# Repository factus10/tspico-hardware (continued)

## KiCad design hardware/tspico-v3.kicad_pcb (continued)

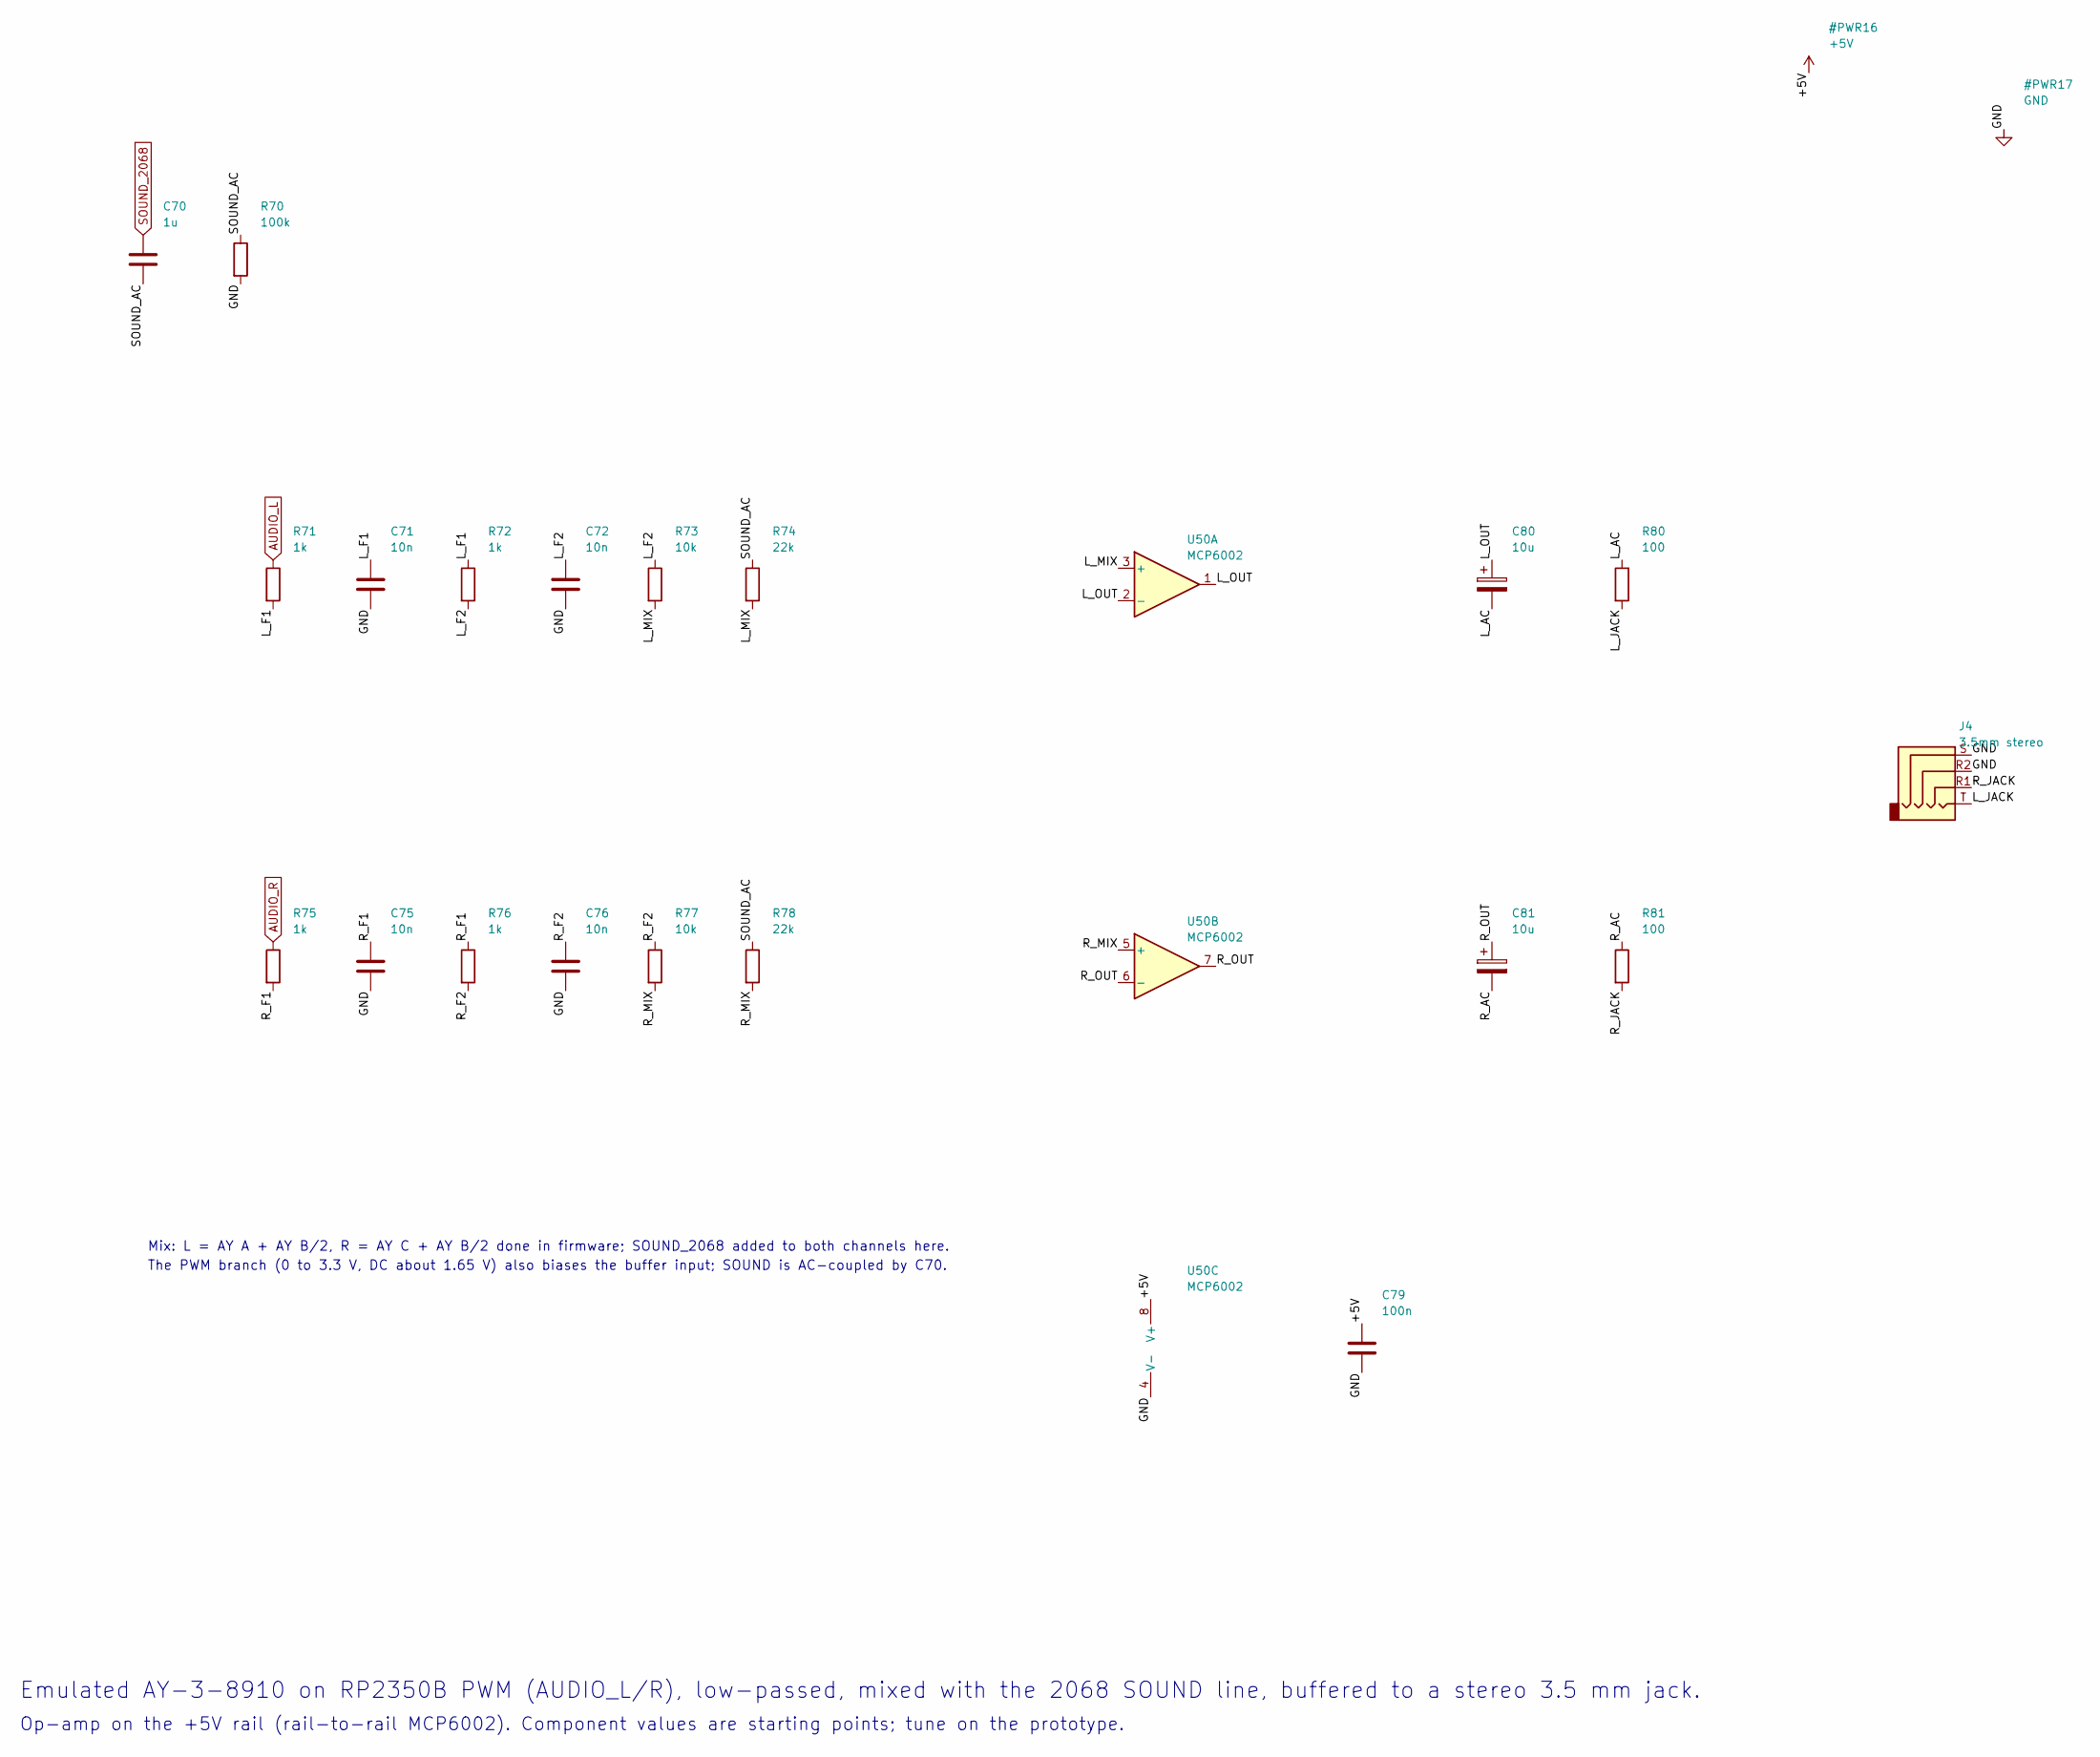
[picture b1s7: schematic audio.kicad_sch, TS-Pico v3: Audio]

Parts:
C70: 1u; C_0603_1608Metric; MPN CL10A105KB8NNNC; LCSC C15849
C71, C72, C75, C76: 10n; C_0603_1608Metric; MPN CL10B103KB8NNNC; LCSC C57112
C79: 100n; C_0603_1608Metric; MPN CC0603KRX7R9BB104; LCSC C14663
C80, C81: 10u; C_0603_1608Metric; MPN CL10A106KP8NNNC; LCSC C19702
J4: 3.5mm stereo; Jack_3.5mm_PJ320D_Horizontal; MPN PJ-320D; LCSC C431535
R70: 100k; R_0603_1608Metric; MPN 0603WAF1003T5E; LCSC C25803
R71, R72, R75, R76: 1k; R_0603_1608Metric; MPN 0603WAF1001T5E; LCSC C21190
R73, R77: 10k; R_0603_1608Metric; MPN 0603WAF1002T5E; LCSC C25804
R74, R78: 22k; R_0603_1608Metric; MPN 0603WAF2202T5E; LCSC C31850
R80, R81: 100; R_0603_1608Metric; MPN 0603WAF1000T5E; LCSC C22775
U50: MCP6002; SOIC-8_3.9x4.9mm_P1.27mm; MPN MCP6002T-I/SN; LCSC C7377

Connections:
+5V: C79.1, U50.8 (V+); also elsewhere on the board
/Audio/L_AC: C80.2, R80.1
/Audio/L_F1: C71.1, R71.2, R72.1
/Audio/L_F2: C72.1, R72.2, R73.1
/Audio/L_JACK: J4.T, R80.2
/Audio/L_MIX: R73.2, R74.2, U50.3 (+)
/Audio/L_OUT: C80.1, U50.1, U50.2 (-)
/Audio/R_AC: C81.2, R81.1
/Audio/R_F1: C75.1, R75.2, R76.1
/Audio/R_F2: C76.1, R76.2, R77.1
/Audio/R_JACK: J4.R1, R81.2
/Audio/R_MIX: R77.2, R78.2, U50.5 (+)
/Audio/R_OUT: C81.1, U50.6 (-), U50.7
/Audio/SOUND_AC: C70.2, R70.1, R74.1, R78.1
AUDIO_L: R71.1; also elsewhere on the board
AUDIO_R: R75.1; also elsewhere on the board
SOUND_2068: C70.1; also elsewhere on the board

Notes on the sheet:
Emulated AY-3-8910 on RP2350B PWM (AUDIO_L/R), low-passed, mixed with the 2068 SOUND line, buffered to a stereo 3.5 mm jack.
Op-amp on the +5V rail (rail-to-rail MCP6002). Component values are starting points; tune on the prototype.
Mix: L = AY A + AY B/2, R = AY C + AY B/2 done in firmware; SOUND_2068 added to both channels here.
The PWM branch (0 to 3.3 V, DC about 1.65 V) also biases the buffer input; SOUND is AC-coupled by C70.

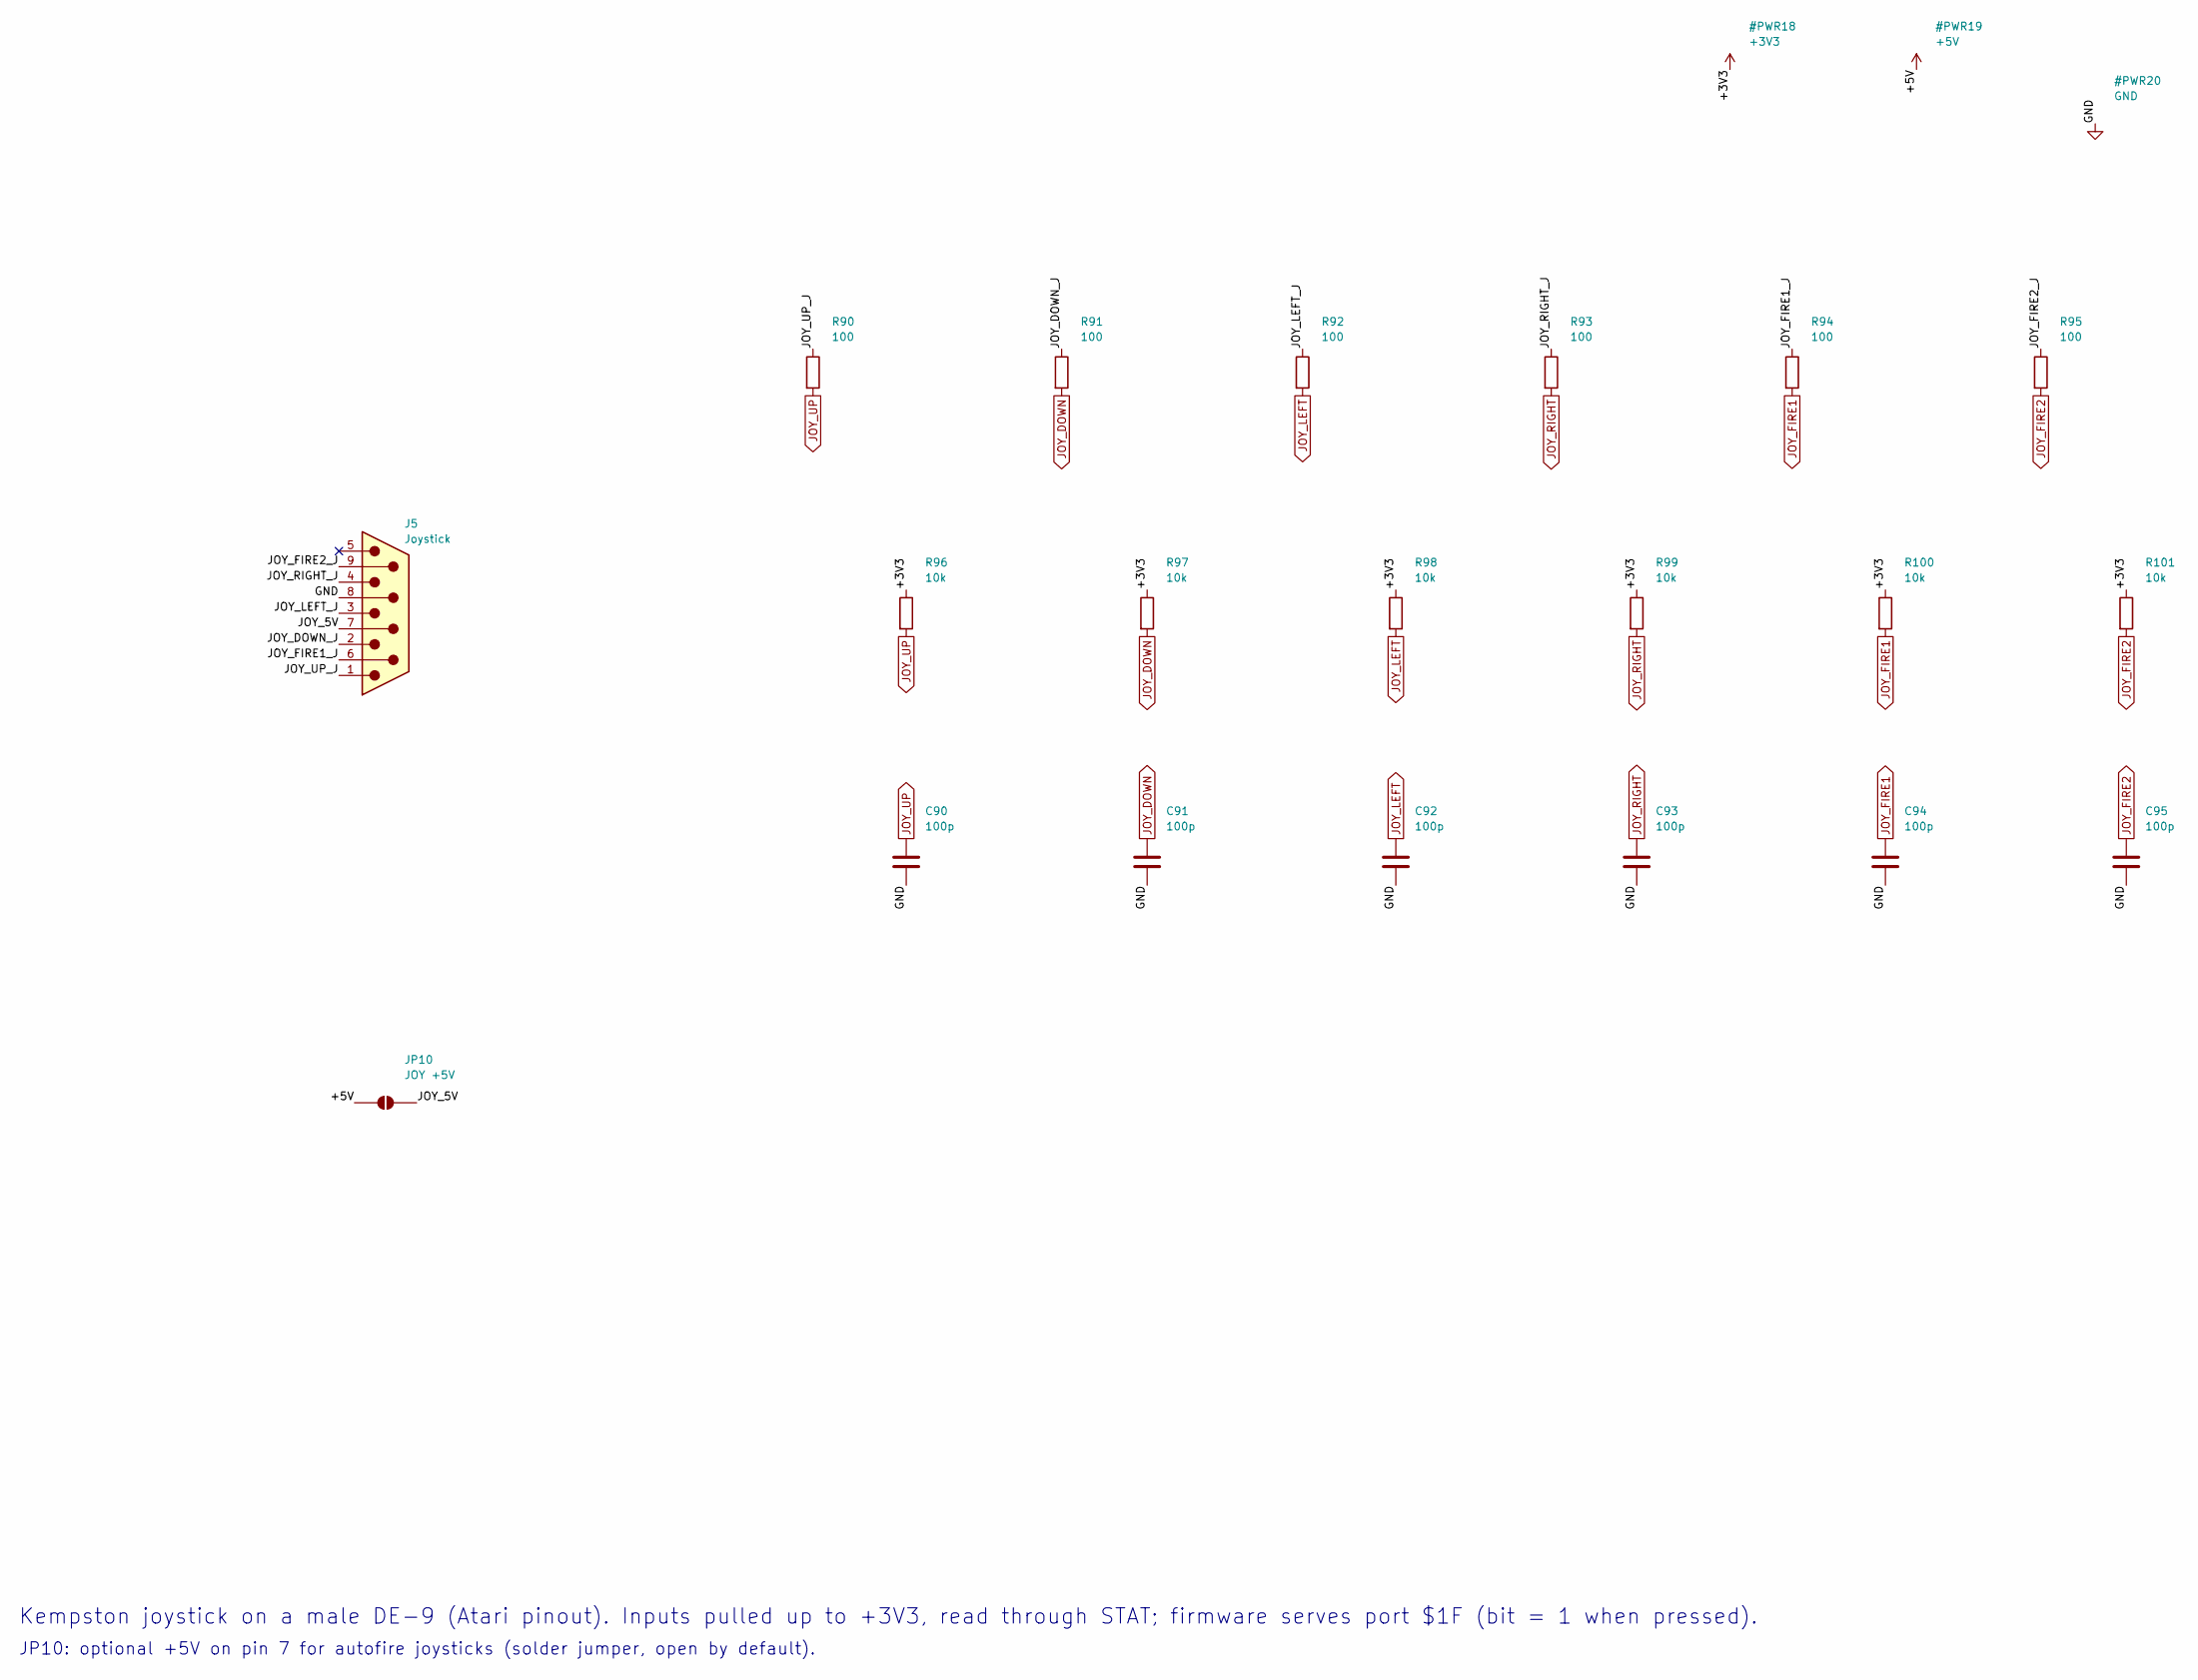
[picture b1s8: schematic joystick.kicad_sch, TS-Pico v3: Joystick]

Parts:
C90, C91, C92, C93, C94, C95: 100p; C_0603_1608Metric; MPN CL10C101JB8NNNC; LCSC C14858
J5: Joystick; DSUB-9_Pins_Horizontal_P2.77x2.84mm_EdgePinOffset7.70mm_Hou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; MPN DS1037-09MNAKT74-0CC; LCSC C75750
JP10: JOY +5V; SolderJumper-2_P1.3mm_Open_RoundedPad1.0x1.5mm
R90, R91, R92, R93, R94, R95: 100; R_0603_1608Metric; MPN 0603WAF1000T5E; LCSC C22775
R96, R97, R98, R99, R100, R101: 10k; R_0603_1608Metric; MPN 0603WAF1002T5E; LCSC C25804

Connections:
+3V3: R96.1, R97.1, R98.1, R99.1, R100.1, R101.1; also elsewhere on the board
+5V: JP10.1 (A); also elsewhere on the board
/Joystick/JOY_5V: J5.7, JP10.2 (B)
/Joystick/JOY_DOWN_J: J5.2, R91.1
/Joystick/JOY_FIRE1_J: J5.6, R94.1
/Joystick/JOY_FIRE2_J: J5.9, R95.1
/Joystick/JOY_LEFT_J: J5.3, R92.1
/Joystick/JOY_RIGHT_J: J5.4, R93.1
/Joystick/JOY_UP_J: J5.1, R90.1
JOY_DOWN: C91.1, R91.2, R97.2; also elsewhere on the board
JOY_FIRE1: C94.1, R94.2, R100.2; also elsewhere on the board
JOY_FIRE2: C95.1, R95.2, R101.2; also elsewhere on the board
JOY_LEFT: C92.1, R92.2, R98.2; also elsewhere on the board
JOY_RIGHT: C93.1, R93.2, R99.2; also elsewhere on the board
JOY_UP: C90.1, R90.2, R96.2; also elsewhere on the board

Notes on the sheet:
Kempston joystick on a male DE-9 (Atari pinout). Inputs pulled up to +3V3, read through STAT; firmware serves port $1F (bit = 1 when pressed).
JP10: optional +5V on pin 7 for autofire joysticks (solder jumper, open by default).

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
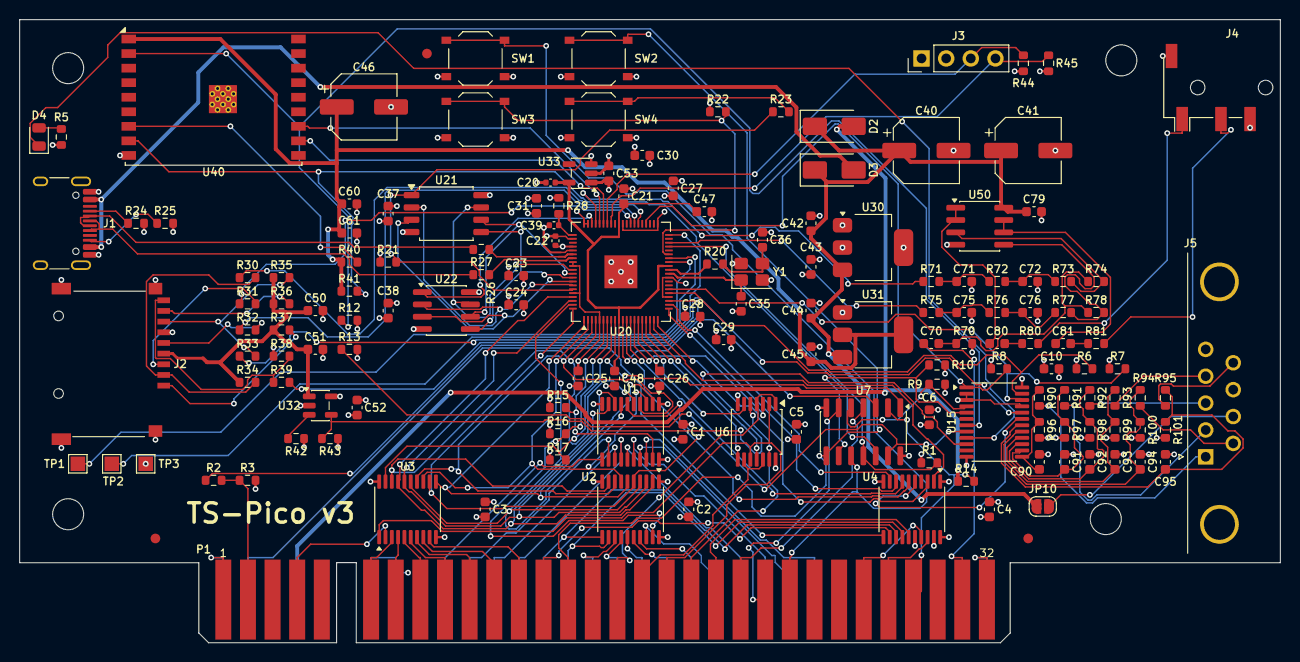
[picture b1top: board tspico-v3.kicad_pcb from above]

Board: 4 copper layers, 130.0 x 64.2 mm, 157 parts (0 on the bottom side), 152 nets.

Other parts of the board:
C53: 1u; C_0603_1608Metric
FID1, FID2, FID3: Fiducial_1mm_Mask2mm
H1, H2, H3, H4: MountingHole_3.2mm_M3
U33: ME6211C12M5G-N; SOT-23-5

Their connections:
+3V3: C53.1, U33.1, U33.3; also elsewhere on the board

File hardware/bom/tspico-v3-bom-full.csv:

"Value","Reference","Footprint","MPN","LCSC","Qty","Fitted by"
"100n","C1-C6,C10,C21,C23-C31,C37,C38,C47,C48,C51,C61,C79","Capacitor_SMD:C_0603_1608Metric","CC0603KRX7R9BB104","C14663","24","JLCPCB"
"4.7u","C20,C22,C39","Capacitor_SMD:C_0402_1005Metric","CL05A475MP5NRNC","C23733","3","JLCPCB"
"15p","C35,C36","Capacitor_SMD:C_0603_1608Metric","CL10C150JB8NNNC","C1644","2","JLCPCB"
"220u","C40,C41,C46","Capacitor_SMD:CP_Elec_6.3x5.4","RVT220UF10V67RV0037","C2833309","3","JLCPCB"
"10u","C42-C45,C50,C60,C80,C81","Capacitor_SMD:C_0603_1608Metric","CL10A106KP8NNNC","C19702","8","JLCPCB"
"1u","C52,C53,C70","Capacitor_SMD:C_0603_1608Metric","CL10A105KB8NNNC","C15849","3","JLCPCB"
"10n","C71,C72,C75,C76","Capacitor_SMD:C_0603_1608Metric","CL10B103KB8NNNC","C57112","4","JLCPCB"
"100p","C90-C95","Capacitor_SMD:C_0603_1608Metric","CL10C101JB8NNNC","C14858","6","JLCPCB"
"SS34","D2,D3","Diode_SMD:D_SMA","SS34","C8678","2","JLCPCB"
"green","D4","LED_SMD:LED_0805_2012Metric","KT-0805G","C2297","1","JLCPCB"
"USB-C","J1","Connector_USB:USB_C_Receptacle_HRO_TYPE-C-31-M-12","TYPE-C-31-M-12","C165948","1","JLCPCB"
"microSD","J2","tspico:microSD_TF-01A","TF-01A","C91145","1","JLCPCB"
"OLED 1.54in 128x64 I2C","J3","Connector_PinHeader_2.54mm:PinHeader_1x04_P2.54mm_Vertical","2.54-1x40P (cut to 4)","C2337","1","hand"
"3.5mm stereo","J4","Connector_Audio:Jack_3.5mm_PJ320D_Horizontal","PJ-320D","C431535","1","JLCPCB"
"Joystick","J5","Connector_Dsub:DSUB-9_Pins_Horizontal_P2.77x2.84mm_EdgePinOffset7.70mm_Housed_MountingHolesOffset9.12mm","DS1037-09MNAKT74-0CC","C75750","1","hand"
"JOY +5V","JP10","Jumper:SolderJumper-2_P1.3mm_Open_RoundedPad1.0x1.5mm","","","1","none (board feature)"
"TS2068_Edge","P1","tspico:TS2068_EdgeConnector_2x32","","","1","none (board feature)"
"4k7","R1,R2,R6,R7,R44,R45","Resistor_SMD:R_0603_1608Metric","0603WAF4701T5E","C23162","6","JLCPCB"
"1k","R3,R20,R23,R71,R72,R75,R76","Resistor_SMD:R_0603_1608Metric","0603WAF1001T5E","C21190","7","JLCPCB"
"100","R5,R80,R81,R90-R95","Resistor_SMD:R_0603_1608Metric","0603WAF1000T5E","C22775","9","JLCPCB"
"10k","R8-R10,R12,R13,R15-R17,R21,R22,R34-R38,R40,R41,R43,R73,R77,R96-R101","Resistor_SMD:R_0603_1608Metric","0603WAF1002T5E","C25804","26","JLCPCB"
"2k2","R14","Resistor_SMD:R_0603_1608Metric","0603WAF2201T5E","C4190","1","JLCPCB"
"5k1","R24,R25","Resistor_SMD:R_0603_1608Metric","0603WAF5101T5E","C23186","2","JLCPCB"
"33","R26-R28,R30-R33","Resistor_SMD:R_0603_1608Metric","0603WAF330JT5E","C23140","7","JLCPCB"
"0","R39","Resistor_SMD:R_0603_1608Metric","0603WAF0000T5E","C21189","1","JLCPCB"
"15k","R42","Resistor_SMD:R_0603_1608Metric","0603WAF1502T5E","C22809","1","JLCPCB"
"100k","R70","Resistor_SMD:R_0603_1608Metric","0603WAF1003T5E","C25803","1","JLCPCB"
"22k","R74,R78","Resistor_SMD:R_0603_1608Metric","0603WAF2202T5E","C31850","2","JLCPCB"
"TS Reset","SW1","Button_Switch_SMD:SW_Push_1P1T_XKB_TS-1187A","TS-1187A-B-A-B","C318884","1","JLCPCB"
"NMI","SW2","Button_Switch_SMD:SW_Push_1P1T_XKB_TS-1187A","TS-1187A-B-A-B","C318884","1","JLCPCB"
"RUN","SW3","Button_Switch_SMD:SW_Push_1P1T_XKB_TS-1187A","TS-1187A-B-A-B","C318884","1","JLCPCB"
"BOOTSEL","SW4","Button_Switch_SMD:SW_Push_1P1T_XKB_TS-1187A","TS-1187A-B-A-B","C318884","1","JLCPCB"
"SWCLK","TP1","TestPoint:TestPoint_Pad_1.5x1.5mm","","","1","none (board feature)"
"SWDIO","TP2","TestPoint:TestPoint_Pad_1.5x1.5mm","","","1","none (board feature)"
"GND","TP3","TestPoint:TestPoint_Pad_1.5x1.5mm","","","1","none (board feature)"
"74LVC245APW","U1-U4","Package_SO:TSSOP-20_4.4x6.5mm_P0.65mm","74LVC245APW,118","C6082","4","JLCPCB"
"74LVC32APW","U6","Package_SO:TSSOP-14_4.4x5mm_P0.65mm","74LVC32APW,118","C6087","1","JLCPCB"
"74LVC06AD","U7","Package_SO:SOIC-14_3.9x8.7mm_P1.27mm","EM74LVC06AD","C49188178","1","JLCPCB"
"XL9555","U15","Package_SO:TSSOP-24_4.4x7.8mm_P0.65mm","XL9555","C609791","1","JLCPCB"
"RP2350B","U20","Package_DFN_QFN:QFN-80-1EP_10x10mm_P0.4mm_EP3.4x3.4mm","RP2350B","C42415655","1","JLCPCB"
"GD25Q128ESIGR","U21","Package_SO:SOIC-8_5.3x5.3mm_P1.27mm","GD25Q128ESIGR","C2928891","1","JLCPCB"
"APS6404L-3SQR-SN","U22","Package_SO:SOIC-8_3.9x4.9mm_P1.27mm","APS6404L-3SQR-SN","C5333729","1","hand (DNP)"
"TLV1117LV33","U30,U31","Package_TO_SOT_SMD:SOT-223-3_TabPin2","TLV1117LV33DCYR","C15578","2","JLCPCB"
"SY6280AAC","U32","Package_TO_SOT_SMD:SOT-23-5","SY6280AAC","C55136","1","JLCPCB"
"ME6211C12M5G-N","U33","Package_TO_SOT_SMD:SOT-23-5","ME6211C12M5G-N","C236672","1","JLCPCB"
"ESP32-C3-WROOM-02-N4","U40","RF_Module:ESP32-C3-WROOM-02","ESP32-C3-WROOM-02-N4","C2934560","1","JLCPCB"
"MCP6002","U50","Package_SO:SOIC-8_3.9x4.9mm_P1.27mm","MCP6002T-I/SN","C7377","1","JLCPCB"
"12MHz","Y1","Crystal:Crystal_SMD_3225-4Pin_3.2x2.5mm","ABM8-272-T3","C20625731","1","JLCPCB"

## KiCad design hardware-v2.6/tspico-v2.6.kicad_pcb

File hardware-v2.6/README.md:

# TS-Pico v2.6 KiCad project

The v2.2 card with the RP2040 on the board instead of a Pico module, on the v3 outline (130 x 64.25 mm, 56 mm body plus the 8.25 mm tongue, same edge connector, 4 layers). JLCPCB assembles everything surface mount. The flash and SRAM are the original through-hole DIP-32 parts in sockets, soldered by hand. The bus circuit, the designators and the GPIO map are v2.2's, so the standard Pico MicroPython build and the shipped firmware (tspico-firmware-build) run unchanged.

**To order:** the JLCPCB upload files (Gerber zip, BOM, placement), ordering notes, schematic PDF and renders are on the [v2.6-proto2 release](https://github.com/factus10/tspico-hardware/releases/tag/v2.6-proto2). Prototype 1 (74LS glue and a 555 reset, otherwise the same board) is the [v2.6-proto1 release](https://github.com/factus10/tspico-hardware/releases/tag/v2.6-proto1). To regenerate them from this folder, run `python3 scripts/gen_fab.py` (output in `fab/jlcpcb/`).

Status: see "State" at the end. Not built.

Compared with v2.5 (`../hardware-v2.5/`, Pico module, all SMT, bench programming): same bus logic and layout style. The Pico module is replaced by the RP2040 core, the memories go back to DIP, and the bench-programming block is gone: program the SST39SF040 in a ROM programmer before it goes in its socket, as v2.2 boards are built.

## RP2040 core (sheet `mcu`)

From the minimal design in "Hardware design with RP2040":

- U2 RP2040 (QFN-56). Decoupling: 100 nF per IOVDD pin (C21-C26, one shared with USB_VDD), C27 on ADC_AVDD, 1 uF on VREG_VIN (C28) and VREG_VOUT (C29), 100 nF per DVDD pin (C30, C31).
- U21 W25Q16JVSSIQ, 2 MB QSPI flash, the same size as the Pico's, so the RPI_PICO MicroPython build fits as is.
- Y1 12 MHz ABM8-272-T3 with 15 pF loads (C33, C34) and 1 k (R25) on XOUT. This is the design guide's crystal, and the one that passed v3 bring-up.
- J1 USB-C (HRO TYPE-C-31-M-12, as v3), 5.1 k Rd on CC1/CC2 (R26, R27), 27 R series on D+/D- (R28, R29).
- SW4 BOOTSEL (QSPI_SS to GND through R24, 1 k); SW3 RUN (Pico reset) with R9, as v2.2.
- GPIO map: GP0-GP22 and GP26-GP28 carry v2.2's signals. The four the Pico used internally behave as on the Pico: GP23 to test pad TP3, GP24 VBUS sense (R30 5.6 k / R31 10 k), GP25 LED (D5, R34 470 R; the firmware drives it), GP29 VSYS/3 (R32 200 k / R33 100 k). SWCLK/SWDIO go to TP1/TP2.
- Power: VSYS is the edge +5V through D2 (as v2.2) or USB VBUS through D4 (the Schottky inside the Pico). U22 (AMS1117-3.3) supplies +3V3. As with the Pico, USB powers only the 3.3 V side; the 5 V logic and memories run from the 2068.

## Bus logic and reset (prototype 2)

Prototype 1 copied v2.2's 74LS glue gate for gate. Two of those parts were scarce at JLCPCB (SN74LS09: 56 in stock, XL74LS27: 108), and 74LS is fading generally. Prototype 2 rebuilds the same logic in 74LVC at 3.3 V. Every glue output already ended at a 3.3 V part (the Pico through U7, U6's DIR, or the memories' TTL-level inputs), and LVC inputs take the 2068's 5 V directly.

| Signal (Pico pin) | v2.2 / proto1 | Proto2 |
|---|---|---|
| /+RW (GP14), JP4 port pair | LS27 NOR3 + three LS04 inverters + LS32 | U5 74LVC138: A4-A6 select, /IORQ, A7 and /M1 on the enables; JP4 picks O0 ($00-$0F) or O1 ($10-$1F); then one U4 gate |
| /+W (GP11, U6 DIR) | LS27 NOR3 + LS04 | U4: /+RW-select OR /RD. Same as v2.2's except when /M1, /IORQ and /RD are all low, which a Z80 never does |
| /RDROM (GP1) | two LS32 gates | two U4 (74LVC32) gates |
| /MREQ_G (GP13) | LS32 + LS04 | U1 74LVC1G97 (2:1 mux wired as OR with one inverted input) |
| /BE driver (edge A29) | LS09 open-collector AND | U9 74LVC2G07, two open-drain buffers wired-AND; R3 pull-up to 5 V as before |
| /BE_STAT (GP27) | LS09 gate + R4 pull-up | U7 channel 5 (/BE_IN), push-pull; R4 and R7 gone |
| A14/A15 to the memories | LS157 | U8 74LVC157 |
| Power-on reset | NE555 + Q1 + 7 passives, about 2.4 s | U11 TPS3808G01 supervisor: /RESET low while +5V is under 4.09 V (R1/R5) and for 2.7 s after (C12 470 nF), open-drain |

Equivalence was checked by simulating both netlists gate by gate over every input combination (17 inputs, both JP4 positions, 229,376 legal states): all 12 outputs agree. The only difference is /+W in the state excluded above.

Timing changes, all in the direction of more margin: LVC gates are 3-4 ns against LS's 10-15 ns. In `set_ctrl`, /RDROM now settles about 3 ns after /MREQ_G instead of about 14 ns. /+W and /+RW leave U4 after the same number of gates, because `TS_IO` reads /+W one PIO cycle after /+RW falls; on v2.2, /+W arrived slightly first. Every signal still reaches the Pico through U7, as before. Check `set_ctrl` and `TS_IO` with a logic analyser on the first board.

## Other changes from v2.2

As v2.5, minus the bench programming:

- 74LVC245s in TSSOP, SS14, 25 V ceramics.
- On-board micro SD (HRO TF-01A) with 10 k pull-ups on DAT1/DAT2.
- JP1 and P10 are solder jumpers, closed. JP4 is a 3-pad solder jumper, 1-2 ($00-$0F). JP2/JP3/JP5 are DNP pads for external buttons.
- R12 4.7 k from U6 pin 8 (D6) to GND (the later rework on v2.2 boards); R15/R16 10 k on the memory /CE lines.

## Files and commands

Same scheme as v2.5 (see `../hardware-v2.5/README.md`): `scripts/gen_schematic.py` writes the root sheet and the `interface`, `logic`, `memory` and `mcu` sheets; `scripts/gen_layout.py` places the board; `scripts/flow.py` routes it with Freerouting 2.4.1; `scripts/gen_fab.py` writes `fab/jlcpcb/`; `scripts/check.sh` runs ERC and DRC.

```bash
cd hardware-v2.6
PY=/Applications/KiCad/KiCad.app/Contents/Frameworks/Python.framework/Versions/Current/bin/python3
python3 scripts/gen_schematic.py
$PY scripts/flow.py --jar <freerouting-2.4.1.jar>
python3 scripts/gen_fab.py
scripts/check.sh
```

## Layout

- Top left: the RP2040 block. USB-C comes out of the left edge, the QSPI flash sits below it and the crystal to the right of the chip. The decoupling caps ring the package.
- Top strip: BOOTSEL, the regulator, D2/D4, the 3.3 V pull-ups, then the three buttons with their DNP pads.
- Middle band: the two DIP-32 sockets lie along the board, SRAM (U13) on the left and flash (U10) on the right.
- Left edge: micro SD below the MCU block.
- Glue row across the board: U5 (decode) and JP4, U4, U1, U9 with R8/R3/JP1, U8, U7; the TPS3808 reset (U11) to the right of it, below the flash socket.
- Over the data fingers: U6 and R12.
- Every used bottom-side finger has a locked stub and via into the body, as in v2.5.
- Labels: "TS-Pico v2.6" on top above the fingers. On the bottom: the name, the repository URL, the licence (CERN-OHL-S-2.0) and the OSHW logo. They are placed by `../hardware/scripts/labels.py v2.6`, which `flow.py` runs as its last step and which can be rerun on its own.

## Before ordering

- Hand-soldered and not in the JLCPCB BOM: U10 (SST39SF040-70-4C-PHE) and U13 (AS6C4008-55PCN), plus two 32-pin 600 mil DIP sockets.
- Check rotations in JLCPCB's placement preview, especially U2's pin 1, Y1, J1 and U22.
- The TF-01A footprint and card-detect are the same open items as v3.

## State

Prototype 2, 2026-10-11: ERC clean and board DRC clean at every severity (no errors, no warnings, nothing unconnected); `scripts/check.sh` passes. Routed by `flow.py` on its first attempt with no hand edits: 1870 track segments and 310 vias (all 0.6/0.3 mm), every track on F.Cu or B.Cu, so both planes are unbroken; narrowest track 0.15 mm. All 86 designators on silkscreen.

What it took: the first three routing attempts each left one net open, all around the RP2040's top and bottom pin rows (pin 33 +3V3, A14_B on GP22, A0_L on GP10). The caps for the four IOVDD pins there (C21, C22, C24, C25) now stand on their own pin's lane, and `gen_layout.py` pre-routes each pin to its cap as a locked stub, so no neighbour is boxed in.

Compared with prototype 1: 74 assembled parts instead of 81 (93 footprints instead of 100), no 74LS, no 555, no part with less than about 2,400 in stock at JLCPCB on 2026-10-11. JLC parts plus loading fees: $9.79 per board on a 10-board run ($6.19 parts, $36 fees once; prototype 1 was $9.43), not counting the hand-soldered DIP memories and sockets. Renders in `renders/`.

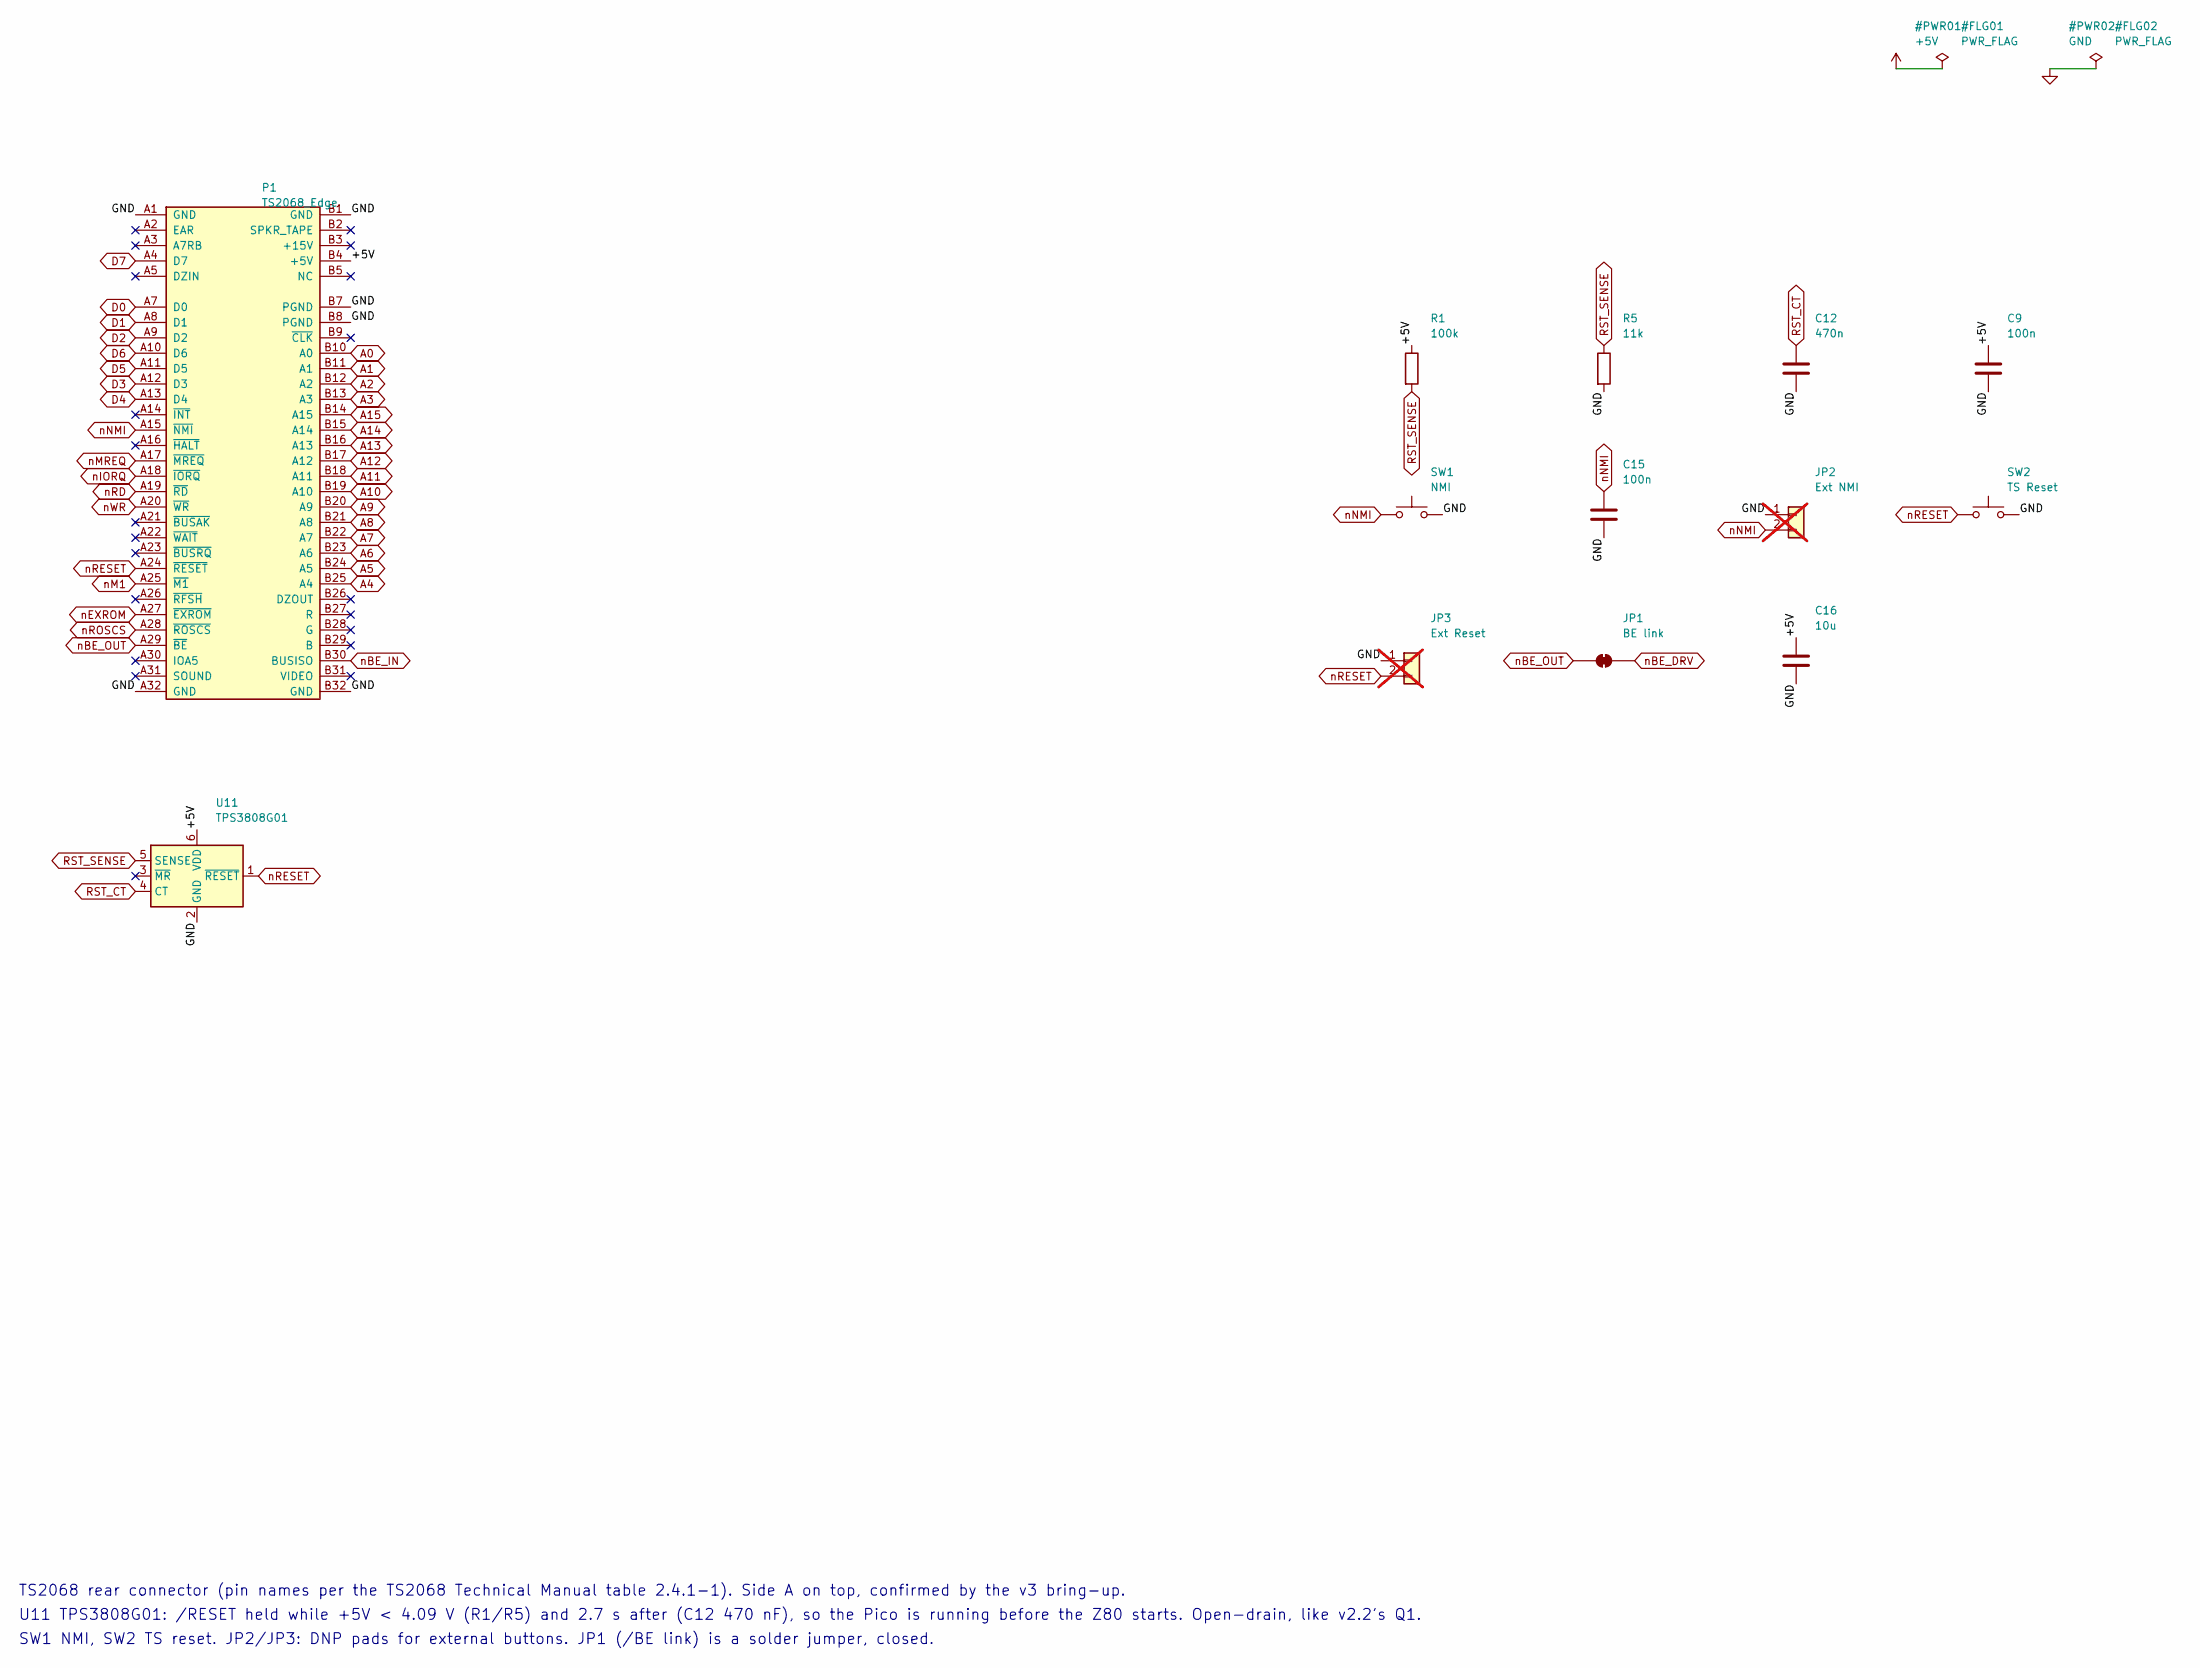
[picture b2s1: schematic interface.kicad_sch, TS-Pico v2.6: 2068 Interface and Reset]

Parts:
C9, C15: 100n; C_0603_1608Metric; MPN CC0603KRX7R9BB104; LCSC C14663
C12: 470n; C_0603_1608Metric; MPN CL10B474KA8NNNC; LCSC C1623
C16: 10u; C_0805_2012Metric; MPN CL21A106KAYNNNE; LCSC C15850
JP1: BE link; SolderJumper-2_P1.3mm_Bridged_RoundedPad1.0x1.5mm
JP2: Ext NMI; PinHeader_1x02_P2.54mm_Vertical_SMD_Pin1Left; not fitted
JP3: Ext Reset; PinHeader_1x02_P2.54mm_Vertical_SMD_Pin1Left; not fitted
P1: TS2068_Edge; TS2068_EdgeConnector_2x32
R1: 100k; R_0603_1608Metric; MPN 0603WAF1003T5E; LCSC C25803
R5: 11k; R_0603_1608Metric; MPN 0603WAF1102T5E; LCSC C25950
SW1: NMI; SW_Push_1P1T_XKB_TS-1187A; MPN TS-1187A-B-A-B; LCSC C318884
SW2: TS Reset; SW_Push_1P1T_XKB_TS-1187A; MPN TS-1187A-B-A-B; LCSC C318884
U11: TPS3808G01; SOT-23-6; MPN TPS3808G01DBVR; LCSC C19653

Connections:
+5V: C9.1, C16.1, P1.B4 (+5V), R1.1, U11.6 (VDD); also elsewhere on the board
A0: P1.B10 (A0); also elsewhere on the board
A1: P1.B11 (A1); also elsewhere on the board
A2: P1.B12 (A2); also elsewhere on the board
A3: P1.B13 (A3); also elsewhere on the board
A4: P1.B25 (A4); also elsewhere on the board
A5: P1.B24 (A5); also elsewhere on the board
A6: P1.B23 (A6); also elsewhere on the board
A7: P1.B22 (A7); also elsewhere on the board
A8: P1.B21 (A8); also elsewhere on the board
A9: P1.B20 (A9); also elsewhere on the board
A10: P1.B19 (A10); also elsewhere on the board
A11: P1.B18 (A11); also elsewhere on the board
A12: P1.B17 (A12); also elsewhere on the board
A13: P1.B16 (A13); also elsewhere on the board
A14: P1.B15 (A14); also elsewhere on the board
A15: P1.B14 (A15); also elsewhere on the board
D0: P1.A7 (D0); also elsewhere on the board
D1: P1.A8 (D1); also elsewhere on the board
D2: P1.A9 (D2); also elsewhere on the board
D3: P1.A12 (D3); also elsewhere on the board
D4: P1.A13 (D4); also elsewhere on the board
D5: P1.A11 (D5); also elsewhere on the board
D6: P1.A10 (D6); also elsewhere on the board
D7: P1.A4 (D7); also elsewhere on the board
GND: C9.2, C12.2, C15.2, C16.2, JP2.1, JP3.1, P1.A1 (GND), P1.A32 (GND), P1.B1 (GND), P1.B7 (PGND), P1.B8 (PGND), P1.B32 (GND), R5.2, SW1.2, SW2.2, U11.2 (GND); also elsewhere on the board
RST_CT: C12.1, U11.4 (CT)
RST_SENSE: R1.2, R5.1, U11.5 (SENSE)
nBE_DRV: JP1.2 (B); also elsewhere on the board
nBE_IN: P1.B30 (BUSISO); also elsewhere on the board
nBE_OUT: JP1.1 (A), P1.A29 (~BE)
nEXROM: P1.A27 (~EXROM); also elsewhere on the board
nIORQ: P1.A18 (~IORQ); also elsewhere on the board
nM1: P1.A25 (~M1); also elsewhere on the board
nMREQ: P1.A17 (~MREQ); also elsewhere on the board
nNMI: C15.1, JP2.2, P1.A15 (~NMI), SW1.1
nRD: P1.A19 (~RD); also elsewhere on the board
nRESET: JP3.2, P1.A24 (~RESET), SW2.1, U11.1 (~RESET)
nROSCS: P1.A28 (~ROSCS); also elsewhere on the board
nWR: P1.A20 (~WR); also elsewhere on the board

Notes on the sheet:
TS2068 rear connector (pin names per the TS2068 Technical Manual table 2.4.1-1). Side A on top, confirmed by the v3 bring-up.
U11 TPS3808G01: /RESET held while +5V < 4.09 V (R1/R5) and 2.7 s after (C12 470 nF), so the Pico is running before the Z80 starts. Open-drain, like v2.2's Q1.
SW1 NMI, SW2 TS reset. JP2/JP3: DNP pads for external buttons. JP1 (/BE link) is a solder jumper, closed.
